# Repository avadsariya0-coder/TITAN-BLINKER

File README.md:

# TITAN BLINKER
Custom LED blinker with mechanical switches built using the XIAO RP2040.

___________________________________________________________________________________________________________________________________________________________________________

## Overview

Titan Blinker is LED blinker built using XIAO RP2040 microcontroller and mechanical switches. The Titan blinker contains electronics,pcb designing and firmware designing.

Unlike the other LED blinker Titan blinker contains XIAO RP2040 and switches. Most of the blinker uses battery instead of microcontroller but titan blinker uses XIAO RP2040 and switches programmed using Arduino. The switches helps in turning on the different LED's independently. The use of switch trigger different lighting behaviour

These project is built using XIAO RP2040,cherry MX button switch, DSA key caps,3 resistors and LEDs.

___________________________________________________________________________________________________________________________________________________________________________

## Inspiration

The idea of creating Titan Blinker came from idea of creating a compact and switch controlled LED blinker.I wanted to make the project different thats why I used cherry MX switch which provides tactical feedback and feels awesome and I don't want LEDs to blink continuously like normal blinkers. The use of the MX cherry allows turning on and off of LEDs using switches which seems to be different.

My project is inspired by the project found on the stasis hackclub made by the Meghana Madiraju.

_________________________________________________________________________________________________________________________________________________________________________
## Features 

• Powered by XIAO RP2040 Microconmtroller

• Mechanical cherry MX switch

• Multiple LED blinking modes

• Powered by USB-C 

• Through hole components

• DSA key caps

• interactive LED blinking system 

• Portable and lightweight

• Customised PCB

_________________________________________________________________________________________________________________________________________________________________________

## Gallery

_________________________________________________________________________________________________________________________________________________________________________

## Hardware stack

_________________________________________________________________________________________________________________________________________________________________________
## Bill of Material

[Bill of material titan blinker.csv](https://github.com/user-attachments/files/28665807/Bill.of.material.titan.blinker.csv)

_________________________________________________________________________________________________________________________________________________________________________

## Zine

_________________________________________________________________________________________________________________________________________________________________________

## PCB design

The PCB for Titan blinker was designed using Kicad.The board contains XIAO RP2040 microcontroller,Mechanical switches,Through hole LEDs and resistors.

Features:

• Through hole component

• LED indicators

• USB-C powered microcontroller

• Mechanical switches

_________________________________________________________________________________________________________________________________________________________________________

## PCB

_________________________________________________________________________________________________________________________________________________________________________

## Schematic

_________________________________________________________________________________________________________________________________________________________________________

## wiring diagram

_________________________________________________________________________________________________________________________________________________________________________

## Enclosure

The enclosure is built using fusion 360. The enclosure contains transparent design.

The design is based on two part construction consisting of removable top and bottom. 

Features:

• USB-C port opening

• LED visibility

• Screw based enclosure

• Switch cutouts

_________________________________________________________________________________________________________________________________________________________________________

## Firmware 

The firmware for the Titan blinker was designed using Arduino IDE.

Features:

• Press button 1 to toggle LED 1

• Press button 2 after button 1 within 2 second LED 2 on

• Press button 3 for 2 seconds to on the LED 3

• Double press button 3 to turn off LED 3

_________________________________________________________________________________________________________________________________________________________________________

## Assembly guide

1. Mount the pcb inside the enclosure using the screws.
2. Insert cherry mx switches to the PCB.
3. Add DSA keycaps to it.

4. attach the XIAO RP2040 to the PCB.

5. Add resistors and LEDs througn the hole.

6. Connect the XIAO RP2040 with the usb c connector and upload the firmware using Arduino.
   Steps to be followed:

   i.Install Aruino IDE.

   2. Install RP2040 board package.

   3. Connect XIAO RP2040 using USB-C

   4. Open the firmware.ino file.

   5. Select the correct Communication port(COM)

   6. Upload the firmware

7. Testing the firmware:

   i. Press button1 to toggle led1 .

   ii. Press button2 after pressing button 1 within 2 sec.

   iii. Press button3 for 2 second and Led3 will turn on.

   iv. Press button 3 twice to turn of Led3.

   if these works properly u are done with your firmware.
   
8. Close the enclosure using lid and the screw. 

_________________________________________________________________________________________________________________________________________________________________________
## Contributing

Contributions,suggestions, and feedback are welcome

If you'd like to improve Titan blinker
1. Fork or clone the repository

https://github.com/avadsariya0-coder/TITAN-BLINKER

2. Create your Feature branch

3. Commit your changes

4. Open a pull request.

_________________________________________________________________________________________________________________________________________________________________________

## Creator

# Arman Vadsariya

17•India•Fallout

_________________________________________________________________________________________________________________________________________________________________________

## License

This project is licensed under MIT License.

_________________________________________________________________________________________________________________________________________________________________________

# Titan Blinker

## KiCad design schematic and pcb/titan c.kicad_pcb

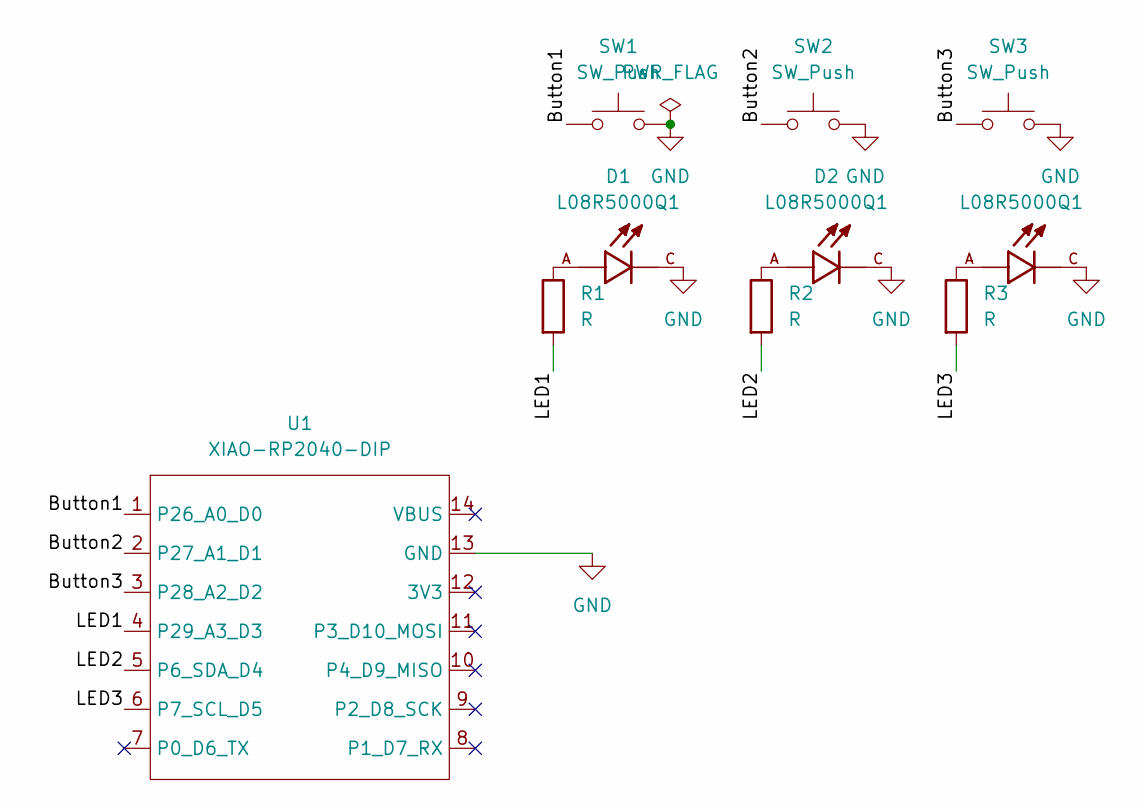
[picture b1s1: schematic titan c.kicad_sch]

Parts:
D1, D2, D3: L08R5000Q1; LEDRD254W57D500H1070; PARTREV NA
R1, R2, R3: R; R_Axial_DIN0204_L3.6mm_D1.6mm_P5.08mm_Horizontal
SW1, SW2, SW3: SW_Push; SW_Cherry_MX_1.00u_PCB
U1: XIAO-RP2040-DIP

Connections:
/Button1: SW1.1, U1.1 (P26_A0_D0)
/Button2: SW2.1, U1.2 (P27_A1_D1)
/Button3: SW3.1, U1.3 (P28_A2_D2)
/LED1: R1.2, U1.4 (P29_A3_D3)
/LED2: R2.2, U1.5 (P6_SDA_D4)
/LED3: R3.2, U1.6 (P7_SCL_D5)
GND: D1.C, D2.C, D3.C, SW1.2, SW2.2, SW3.2, U1.13 (GND)
unnamed: D1.A, R1.1
unnamed: D2.A, R2.1
unnamed: D3.A, R3.1

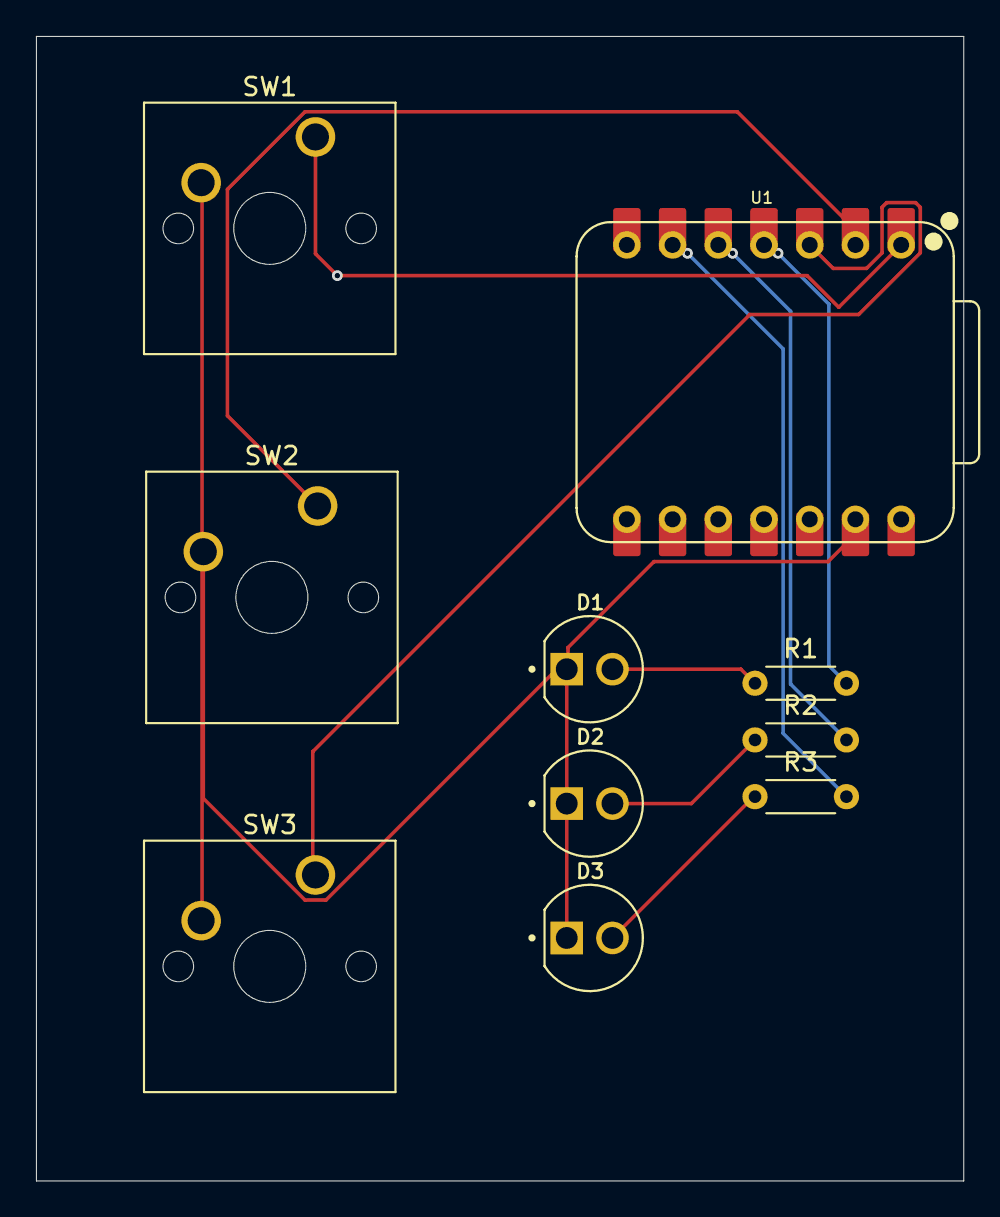
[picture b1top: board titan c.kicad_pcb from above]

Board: 2 copper layers, 51.5 x 63.6 mm, 10 parts (0 on the bottom side), 10 nets.

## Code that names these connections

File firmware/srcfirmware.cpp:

#include <Arduino.h>

const int Button1 = D0;
const int Button2 = D1;
const int Button3 = D2;
const int LED1 = D3;
const int LED2 = D4;
const int LED3 = D5;

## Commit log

2026-05-24 Create LICENSE
2026-05-24 Update README with Titan Blinker details
    Added project description and overview for Titan Blinker.
2026-05-24 Refactor README structure and content
    Updated README to improve formatting and clarity.
2026-05-24 Update README with contributing section
    Added contributing guidelines and improved formatting.
2026-05-25 Update README with assembly steps for Titan Blinker
    Added assembly instructions for the Titan Blinker.
2026-05-25 Enhance README with assembly images
    Added images to the assembly instructions for clarity.
2026-05-25 Fix formatting of installation steps in README
2026-05-25 Revise firmware testing steps and fix numbering
    Updated the steps for testing firmware and corrected numbering.
2026-05-25 Add wiring diagram section to README
    Added wiring diagram image to README.
2026-06-02 Update image in Zine section of README
2026-06-06 Update Bill of Material link and image in README
    Updated the link to the Bill of Material CSV and replaced the image.
2026-06-06 Update Bill of Material link in README
